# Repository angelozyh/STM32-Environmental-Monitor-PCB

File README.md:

# STM32 Environmental Monitor PCB

A custom 2-layer PCB designed in KiCad for an STM32-based environmental monitoring system. The board integrates an STM32 NUCLEO-F303K8, BME280 environmental sensor, dual SN74HC595 shift registers, a 4-digit 7-segment display, transistor-based digit drivers, and a pushbutton interface.

This project is the hardware implementation of my previously breadboarded STM32 environmental monitoring system. The project involved transitioning the working prototype to a custom PCB through schematic capture, footprint selection, PCB layout and routing, fabrication, hand assembly, board bring-up, troubleshooting, and final hardware validation.

## Demo

▶️ **[Watch the full project demo on LinkedIn](https://lnkd.in/p/gfJYUWm9)**

The pushbutton cycles the displayed measurement between temperature, humidity, and pressure.

## Features

- STM32 NUCLEO-F303K8 development board
- BME280 temperature, humidity, and pressure sensor
- I2C communication between the STM32 and BME280
- 4-digit common-cathode 7-segment display
- Two SN74HC595 shift registers for display control
- Four NPN transistor low-side digit drivers
- Pushbutton user input
- Timer-interrupt-based display multiplexing
- UART interface for monitoring and debugging
- Socketed Nucleo, BME280, shift registers, and display for easy replacement
- M3 mounting holes for mechanical support

## System Overview

The STM32 reads environmental data from the BME280 over I2C and displays the selected measurement on a multiplexed 4-digit 7-segment display.

Two SN74HC595 shift registers expand the available GPIO and provide the signals required to control the display. Four NPN transistors provide low-side switching for digit selection.

A pushbutton cycles the displayed measurement between:

- Temperature
- Humidity
- Pressure

UART communication is also available for system monitoring and debugging.

## Hardware

| Component | Purpose |
| --- | --- |
| STM32 NUCLEO-F303K8 | Main microcontroller |
| BME280 | Temperature, humidity, and pressure sensing |
| 2x SN74HC595N | Serial-to-parallel output expansion |
| CC56-12SURKWA | 4-digit common-cathode 7-segment display |
| 4x NPN Transistors | Low-side digit switching |
| Pushbutton | User input |
| Resistors | LED current limiting and transistor biasing |
| 100 nF Capacitors | Local decoupling |

## Schematic

The original breadboard circuit was converted into a complete KiCad schematic before PCB layout.

## PCB Design

The PCB was designed in **KiCad 10** as a 2-layer carrier board for the STM32 environmental monitoring system.

### Board Specifications

- 2-layer FR-4 PCB
- 1.6 mm board thickness
- 1 oz outer copper
- Lead-free HASL surface finish
- Front and back ground pours
- Plated through-holes and vias
- 0.8 mm / 0.3 mm drill vias
- Four 3.2 mm NPTH mounting holes for M3 hardware
- Copper keepout regions around metal mounting hardware

The board primarily uses through-hole components to simplify hand assembly, modification, and component replacement.

### 3D Preview

## PCB Design Process

The PCB development process included:

1. Converting the breadboard implementation into a complete KiCad schematic
2. Selecting and verifying component footprints using manufacturer datasheets
3. Creating custom footprints for board-specific components
4. Positioning components based on signal flow and mechanical requirements
5. Routing signals across the front and back copper layers
6. Adding ground planes
7. Adding mounting holes and mechanical copper keepouts
8. Configuring manufacturing constraints
9. Running KiCad Design Rule Checks (DRC)
10. Generating Gerber and Excellon drill files
11. Inspecting the manufacturing files in KiCad Gerber Viewer
12. Verifying the final board using the manufacturer's Gerber preview
13. Hand assembling and soldering the fabricated PCB
14. Performing electrical checks and initial board bring-up
15. Troubleshooting and correcting hardware issues
16. Validating the completed system

## Custom Footprints

Custom KiCad footprints were created where appropriate, including footprints for:

- STM32 NUCLEO-F303K8 carrier connections
- BME280 sensor module
- TO-92 transistor layout

Dimensions, pin spacing, drill sizes, and component orientation were checked against component and module documentation before PCB fabrication.

## Firmware

Firmware was developed in C using STM32CubeIDE and the STM32 HAL.

The firmware includes:

- GPIO control
- I2C communication
- BME280 sensor interfacing
- Timer interrupts
- 7-segment display multiplexing
- SN74HC595 shift-register control
- External button interrupts
- Button debouncing
- UART communication and debugging

## Design Verification

Before generating the manufacturing files, the PCB was checked using KiCad's Design Rule Checker.

Final manufacturing files were also visually inspected to verify:

- Board outline
- Front and back copper
- Ground pours
- Through-hole locations
- Via locations
- PTH and NPTH drill files
- Solder-mask openings
- Silkscreen placement
- Mounting-hole clearances

## Assembly and Board Bring-Up

After fabrication, the PCB was assembled and soldered by hand. Socketed components were used where practical to simplify component replacement and troubleshooting.

Initial bring-up included:

- Visual inspection
- Continuity and short-circuit checks
- Power and ground verification
- STM32 power-up and firmware testing
- BME280 I2C communication testing
- Shift-register testing
- 7-segment display testing
- Pushbutton input testing
- UART debugging

## Hardware Revision

During initial board bring-up, testing identified missing power and ground connections in the shift-register circuitry.

The issue was diagnosed through electrical measurements and inspection of the schematic and PCB connections. Jumper wires were added to provide the required power and ground connections.

After the hardware correction, the board was retested and full system functionality was verified.

The required connections will be incorporated directly into the PCB layout in a future board revision.

## Final Validation

Following the hardware correction, the completed PCB successfully demonstrated:

- BME280 temperature, humidity, and pressure measurements
- I2C communication
- SN74HC595 shift-register operation
- Timer-based 7-segment display multiplexing
- Pushbutton measurement selection
- UART monitoring and debugging
- Stable operation of the assembled system

The final PCB reproduces the functionality of the original breadboard prototype on a dedicated custom board.

## Tools

### Hardware Design and Assembly

- KiCad 10
- Digital multimeter
- Soldering equipment
- KiCad Gerber Viewer

### Embedded Development

- STM32CubeIDE
- STM32CubeMX
- STM32 HAL
- C
- Tera Term
- Git / GitHub

## Project Status

- [x] Breadboard prototype
- [x] Firmware development
- [x] Schematic capture
- [x] Footprint selection and verification
- [x] Custom footprint creation
- [x] PCB placement and routing
- [x] Design Rule Check
- [x] Gerber and drill generation
- [x] Manufacturing file verification
- [x] PCB fabrication
- [x] PCB assembly
- [x] Initial board bring-up
- [x] Hardware troubleshooting and rework
- [x] Hardware validation
- [x] Final demonstration

## Future Improvements

A future PCB revision would incorporate the shift-register power and ground corrections identified during board bring-up directly into the PCB layout.

Additional improvements could include:

- Further optimization of component placement and routing
- Reduction of overall board size
- Improved silkscreen organization
- Additional test points for easier board bring-up and debugging

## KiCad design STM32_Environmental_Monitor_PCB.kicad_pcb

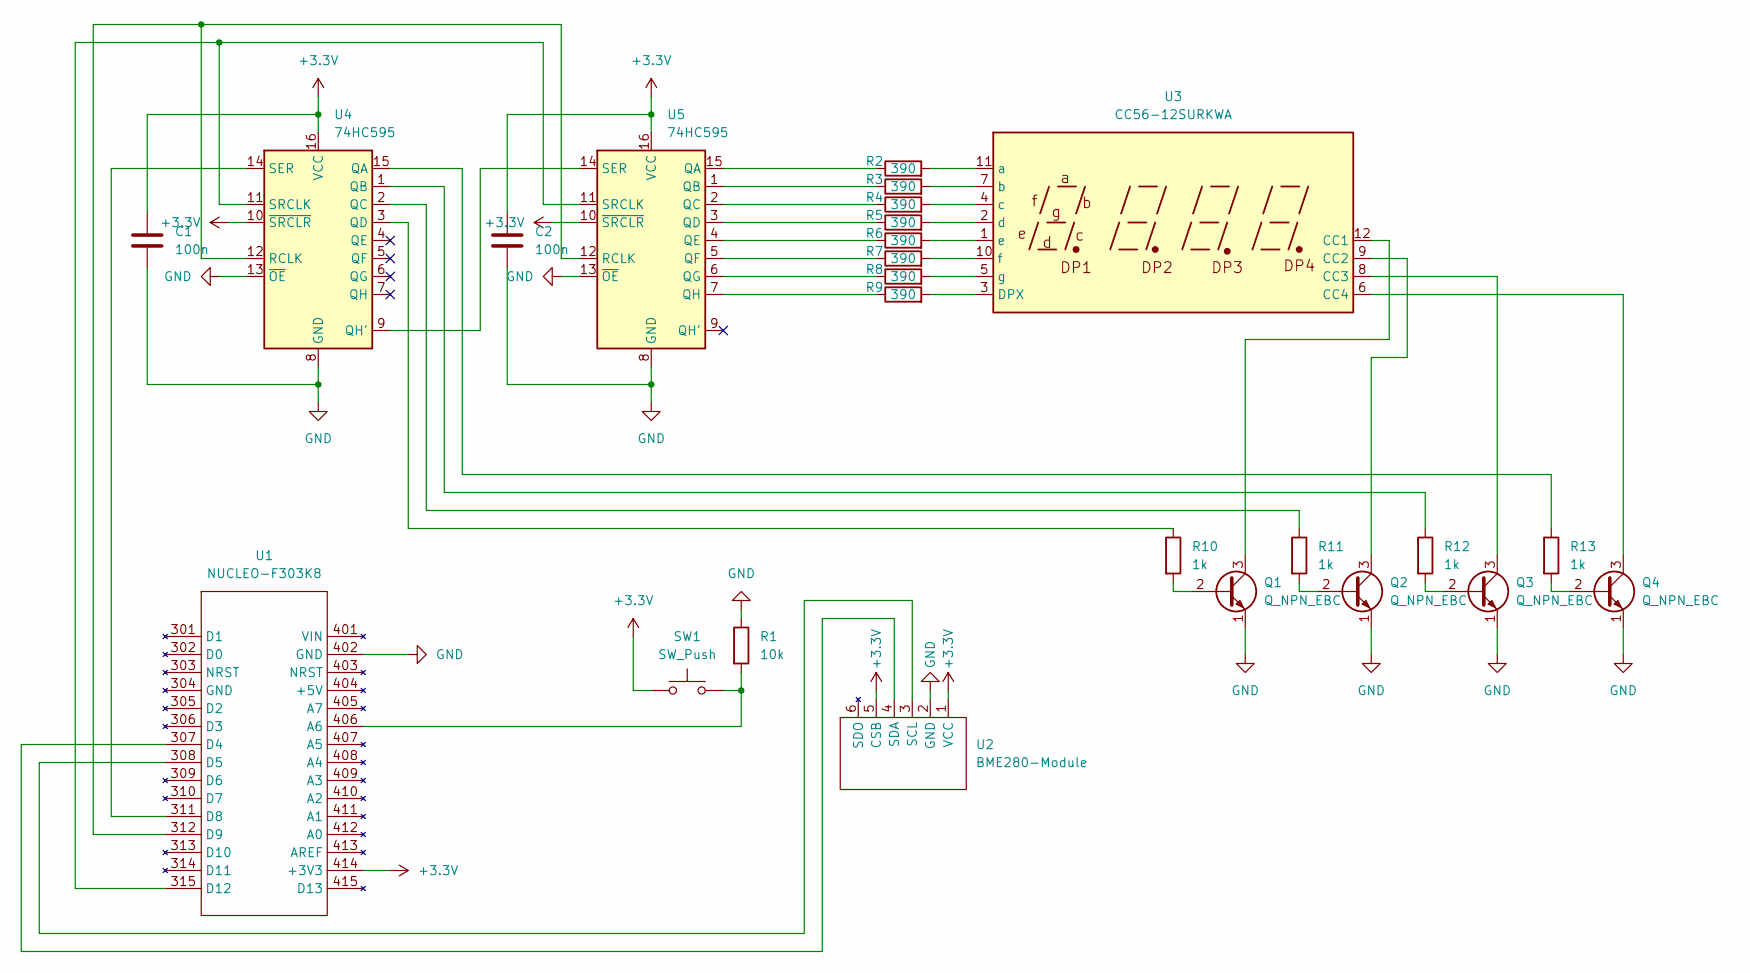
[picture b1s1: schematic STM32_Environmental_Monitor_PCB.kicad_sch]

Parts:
C1, C2: 100n; C_Disc_D4.7mm_W2.5mm_P5.00mm
Q1, Q2, Q3, Q4: Q_NPN_EBC; TO-92_Inline_P1.778mm
R1: 10k; R_Axial_DIN0207_L6.3mm_D2.5mm_P10.16mm_Horizontal
R2, R3, R4, R5, R6, R7, R8, R9: 390; R_Axial_DIN0207_L6.3mm_D2.5mm_P10.16mm_Horizontal
R10, R11, R12, R13: 1k; R_Axial_DIN0207_L6.3mm_D2.5mm_P10.16mm_Horizontal
SW1: SW_Push; SW_PUSH_6mm
U1: NUCLEO-F303K8; NUCLEO-F303K8_Socket
U2: BME280-Module; BME280_Module_Socket
U3: CC56-12SURKWA; CC56-12SURKWA_Socket
U4, U5: 74HC595; DIP-16_W7.62mm_Socket

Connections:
+3.3V: C1.1, C2.1, SW1.1, U1.414 (+3V3), U2.1 (VCC), U2.5 (CSB), U4.10 (~SRCLR), U4.16 (VCC), U5.10 (~SRCLR), U5.16 (VCC)
GND: C1.2, C2.2, Q1.1 (E), Q2.1 (E), Q3.1 (E), Q4.1 (E), R1.1, U1.402 (GND), U2.2 (GND), U4.8 (GND), U4.13 (~OE), U5.8 (GND), U5.13 (~OE)
unnamed: Q1.2 (B), R10.2
unnamed: Q1.3 (C), U3.12 (CC1)
unnamed: Q2.2 (B), R11.2
unnamed: Q2.3 (C), U3.9 (CC2)
unnamed: Q3.2 (B), R12.2
unnamed: Q3.3 (C), U3.8 (CC3)
unnamed: Q4.2 (B), R13.2
unnamed: Q4.3 (C), U3.6 (CC4)
unnamed: R1.2, SW1.2, U1.406 (A6)
unnamed: U1.307 (D4), U2.4 (SDA)
unnamed: U1.308 (D5), U2.3 (SCL)
unnamed: U1.311 (D8), U4.14 (SER)
unnamed: U1.312 (D9), U4.12 (RCLK), U5.12 (RCLK)
unnamed: U1.315 (D12), U4.11 (SRCLK), U5.11 (SRCLK)
unnamed: R9.2, U3.3 (DPX)
unnamed: R2.2, U3.11 (a)
unnamed: R3.2, U3.7 (b)
unnamed: R4.2, U3.4 (c)
unnamed: R5.2, U3.2 (d)
unnamed: R6.2, U3.1 (e)
unnamed: R7.2, U3.10 (f)
unnamed: R8.2, U3.5 (g)
unnamed: R13.1, U4.15 (QA)
unnamed: R12.1, U4.1 (QB)
unnamed: R11.1, U4.2 (QC)
unnamed: R10.1, U4.3 (QD)
unnamed: U4.9 (QH'), U5.14 (SER)
unnamed: R2.1, U5.15 (QA)
unnamed: R3.1, U5.1 (QB)
unnamed: R4.1, U5.2 (QC)
unnamed: R5.1, U5.3 (QD)
unnamed: R6.1, U5.4 (QE)
unnamed: R7.1, U5.5 (QF)
unnamed: R8.1, U5.6 (QG)
unnamed: R9.1, U5.7 (QH)

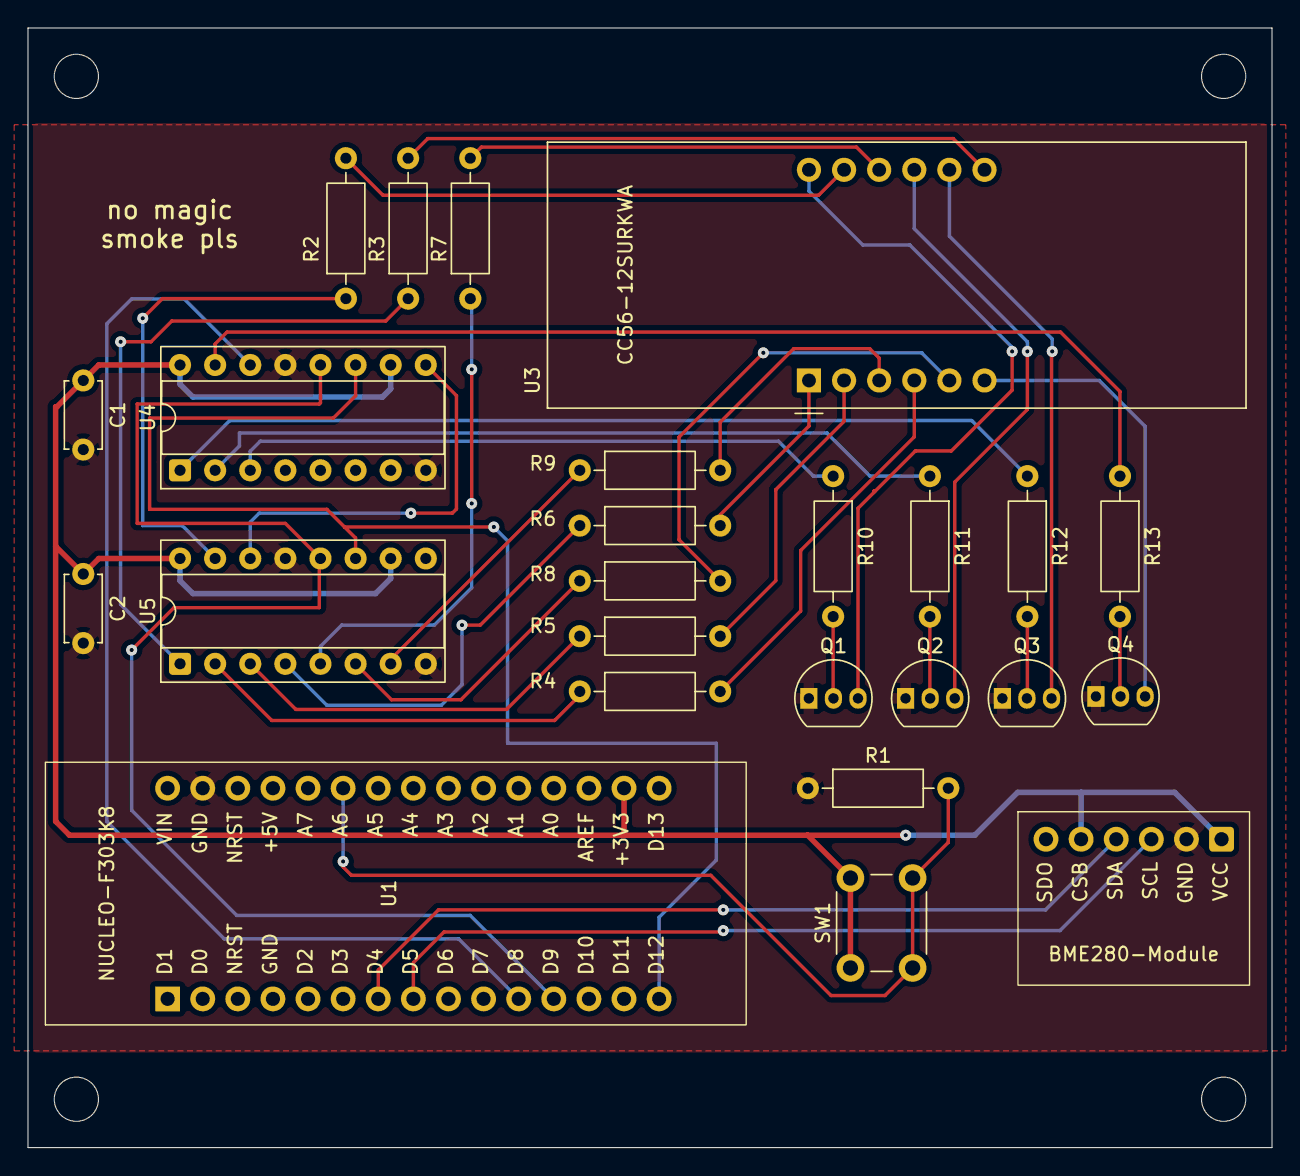
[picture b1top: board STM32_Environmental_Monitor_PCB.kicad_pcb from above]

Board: 2 copper layers, 90.0 x 81.0 mm, 25 parts (0 on the bottom side), 37 nets.
